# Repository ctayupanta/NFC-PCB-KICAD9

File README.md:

# NFC-PCB-KICAD9
Esta es la version 1.0 de mi tarjeta de presentacion. Si quieren las versiones mejoradas pueden visitar mi Patreon.

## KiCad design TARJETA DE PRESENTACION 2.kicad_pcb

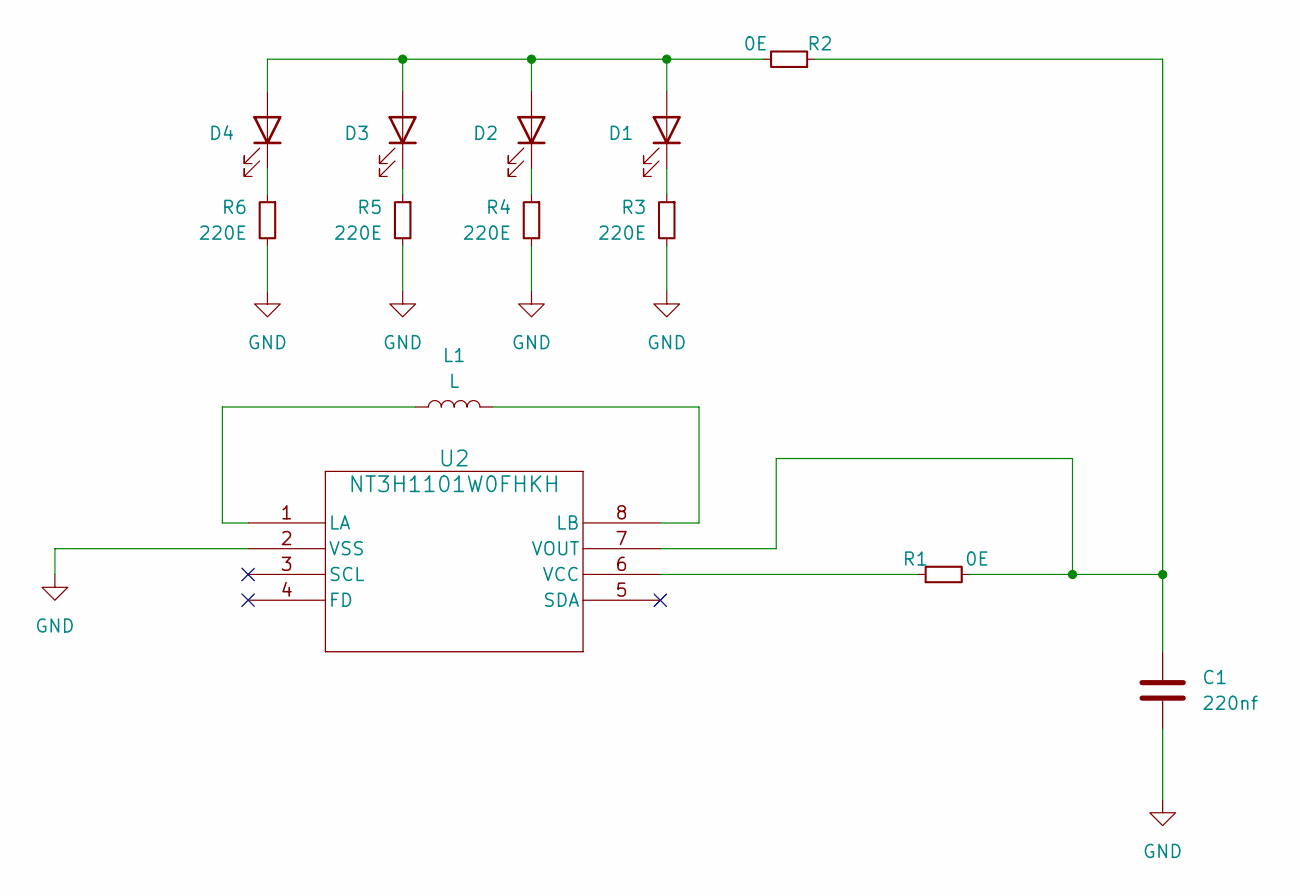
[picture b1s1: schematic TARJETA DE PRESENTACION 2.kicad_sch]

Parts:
C1: 220nf; C_0805_2012Metric; LCSC PN C163697
D1, D2, D3, D4: LED; LED_0805_2012Metric; LCSC PN C19171393
L1: L
R1, R2: 0E; R_0805_2012Metric; LCSC PN C17477
R3, R4, R5, R6: 220E; R_0805_2012Metric; LCSC PN C17557
U2: NT3H1101W0FHKH; XQFN8_NT3H1101_NXP-L; LCSC PN NT3H1101W0FHKH

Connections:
GND: C1.2, R3.2, R4.2, R5.2, R6.2, U2.2 (VSS)
unnamed: D1.2 (A), D2.2 (A), D3.2 (A), D4.2 (A), R2.2
unnamed: D1.1 (K), R3.1
unnamed: D2.1 (K), R4.1
unnamed: D3.1 (K), R5.1
unnamed: D4.1 (K), R6.1
unnamed: L1.1, L1.2, U2.1 (LA), U2.8 (LB)
unnamed: R1.1, U2.6 (VCC)
unnamed: C1.1, R1.2, R2.1, U2.7 (VOUT)

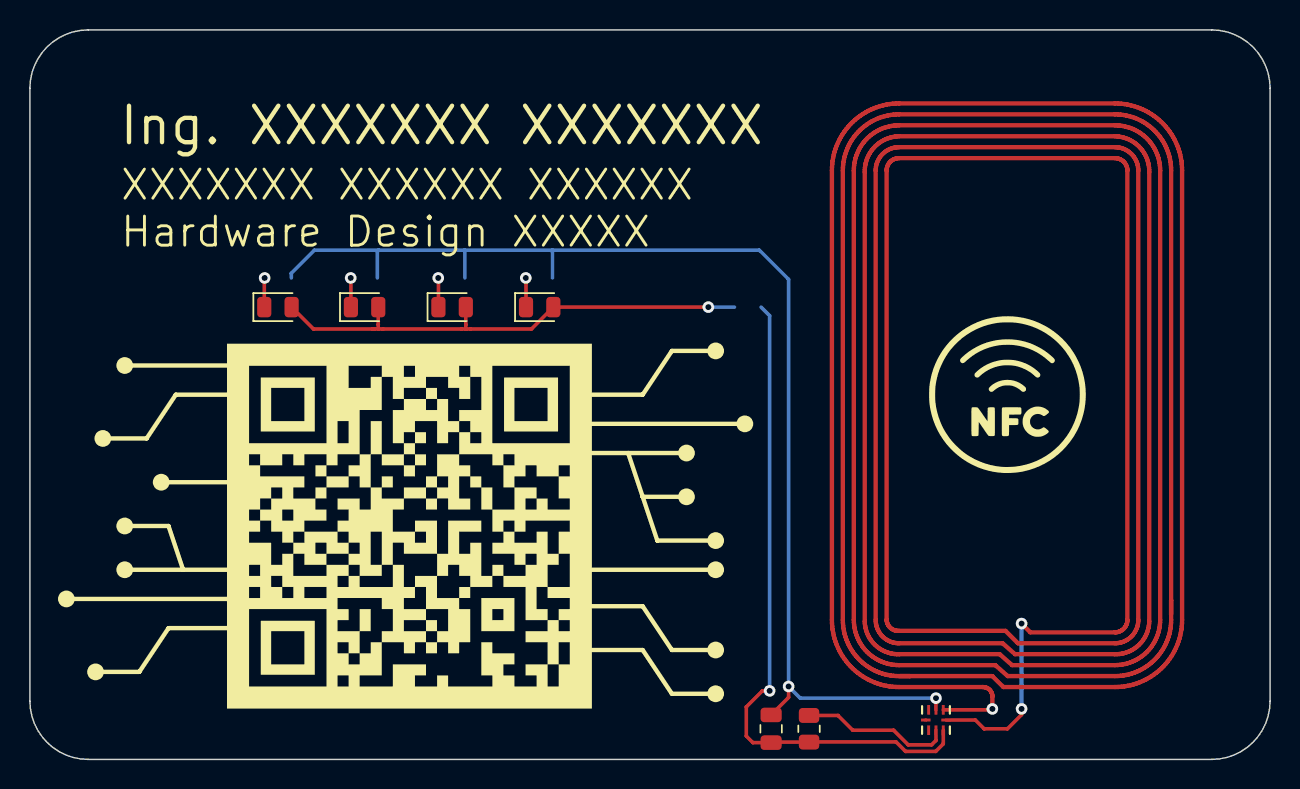
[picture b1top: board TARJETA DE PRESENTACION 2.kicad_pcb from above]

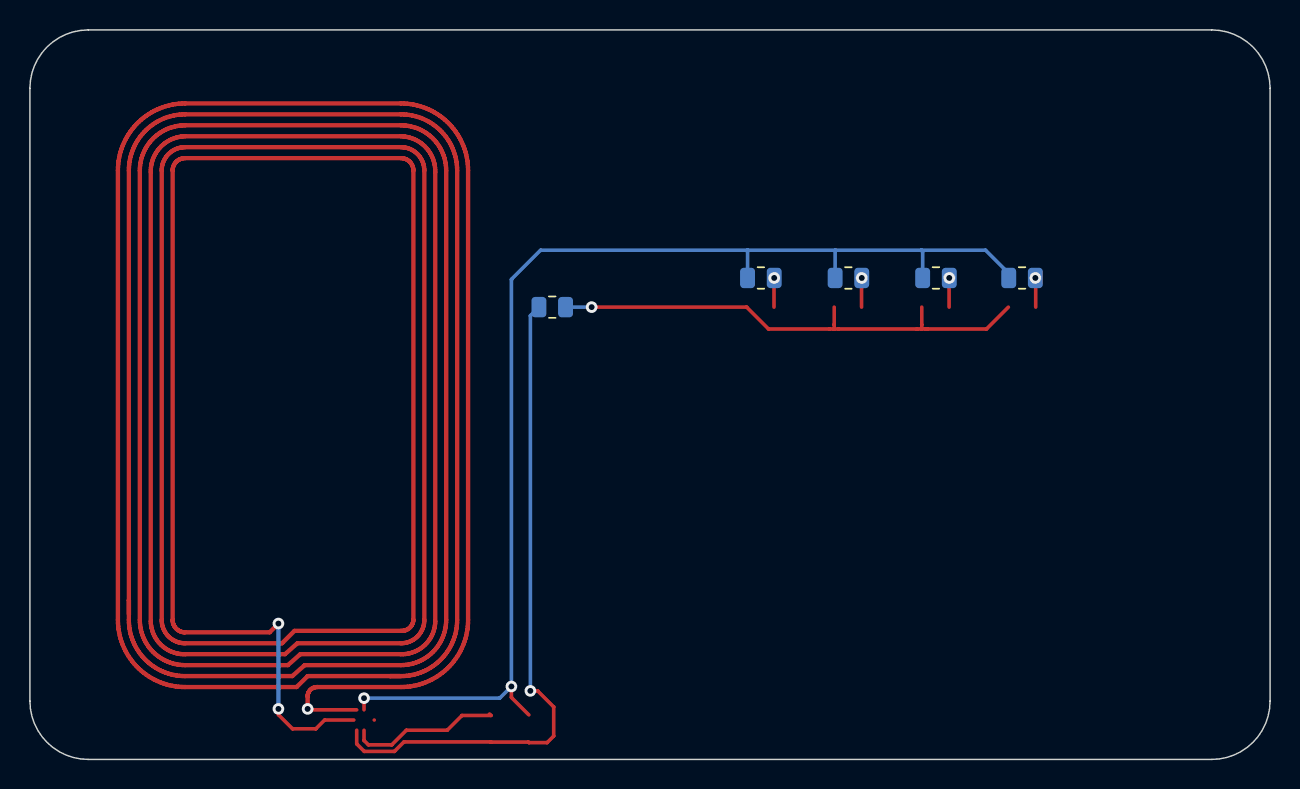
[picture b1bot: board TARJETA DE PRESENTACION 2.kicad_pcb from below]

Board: 2 copper layers, 85.0 x 50.0 mm, 12 parts (5 on the bottom side), 9 nets.

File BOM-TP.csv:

"Reference","Value","Footprint","Qty","DNP","LCSC PN","LINK VENDOR"
"C1","220nf","Capacitor_SMD:C_0805_2012Metric","1","","C163697","https://www.lcsc.com/product-detail/Multilayer-Ceramic-Capac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"
"D1,D2,D3,D4","LED","LED_SMD:LED_0805_2012Metric","4","","C19171393","https://www.lcsc.com/product-detail/span-style-background-co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"
"L1","L","","1","","",""
"R1,R2","0E","Resistor_SMD:R_0805_2012Metric","2","","C17477","https://www.lcsc.com/product-detail/Chip-Resistor-Surface-Mo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"
"R3,R4,R5,R6","220E","Resistor_SMD:R_0805_2012Metric","4","","C17557","https://www.lcsc.com/product-detail/Chip-Resistor-Surface-Mo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"
"U2","NT3H1101W0FHKH","NT3H1101W0FHKH:XQFN8_NT3H1101_NXP-L","1","","NT3H1101W0FHKH","https://www.digikey.com/en/products/detail/nxp-usa-inc/NT3H1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"
